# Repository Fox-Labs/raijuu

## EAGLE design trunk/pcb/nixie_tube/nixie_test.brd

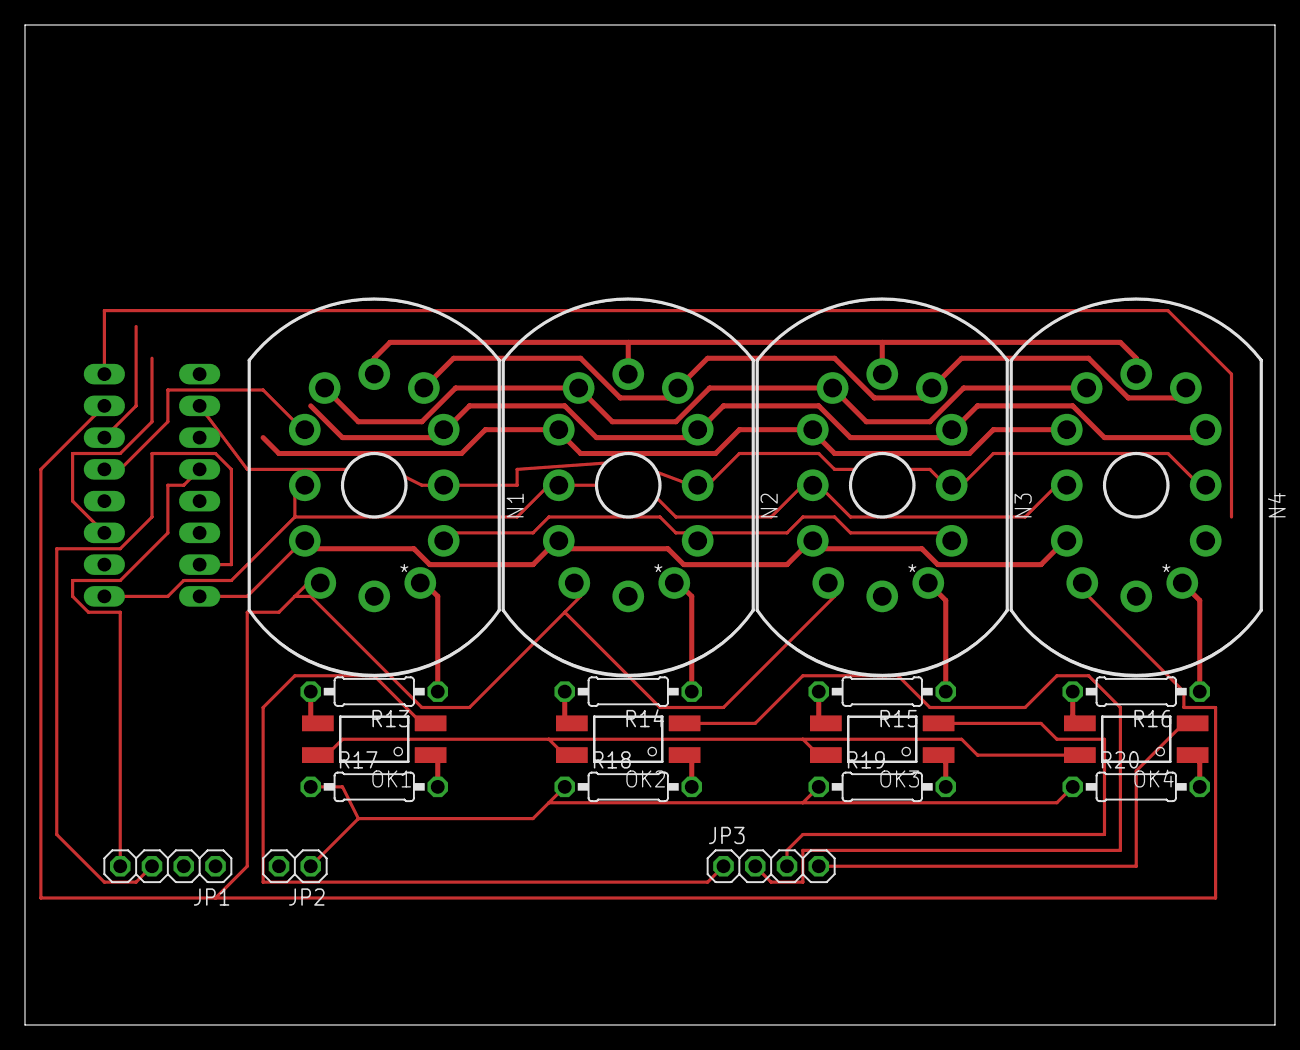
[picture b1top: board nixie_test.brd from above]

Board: 2 copper layers, 100.0 x 80.0 mm, 20 parts (1 on the bottom side), 33 nets.

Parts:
IC1: 74141N; DIL16
JP1, JP3: 1X04
JP2: 1X02
N1, N2, N3, N4: IN-12B; IN-12
OK1, OK2, OK3, OK4: TLP627; 4-SMD
R13, R14, R15, R16, R17, R18, R19, R20: 0207/10

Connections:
+5V: IC1.5, JP2.1, R17.1, R18.1, R19.1, R20.1
+24V: OK1.4, OK2.4, OK3.4, OK4.4
A1: JP3.1, OK1.2
A2: JP3.2, OK2.2
A3: JP3.3, OK3.2
A4: JP3.4, OK4.2
C0: IC1.16, N1.0, N2.0, N3.0, N4.0
C1: IC1.15, N1.1, N2.1, N3.1, N4.1
C2: IC1.8, N1.2, N2.2, N3.2, N4.2
C3: IC1.9, N1.3, N2.3, N3.3, N4.3
C4: IC1.13, N1.4, N2.4, N3.4, N4.4
C5: IC1.14, N1.5, N2.5, N3.5, N4.5
C6: IC1.11, N1.6, N2.6, N3.6, N4.6
C7: IC1.10, N1.7, N2.7, N3.7, N4.7
C8: IC1.1, N1.8, N2.8, N3.8, N4.8
C9: IC1.2, N1.9, N2.9, N3.9, N4.9
GND: IC1.12, JP2.2
unnamed: IC1.3, JP1.1
unnamed: IC1.6, JP1.2
unnamed: IC1.7, JP1.3
unnamed: IC1.4, JP1.4
unnamed: N1.A, R13.1
unnamed: OK1.3, R13.2
unnamed: N2.A, R14.1
unnamed: OK2.3, R14.2
unnamed: N3.A, R15.1
unnamed: OK3.3, R15.2
unnamed: N4.A, R16.1
unnamed: OK4.3, R16.2
unnamed: OK1.1, R17.2
unnamed: OK2.1, R18.2
unnamed: OK3.1, R19.2
unnamed: OK4.1, R20.2

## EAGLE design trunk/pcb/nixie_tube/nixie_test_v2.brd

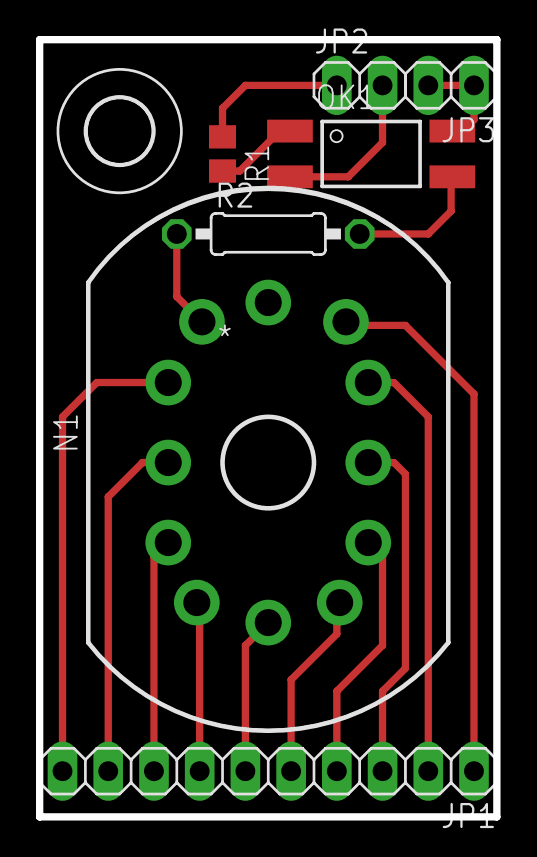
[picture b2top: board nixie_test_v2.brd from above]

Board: 2 copper layers, 25.4 x 43.2 mm, 8 parts (0 on the bottom side), 16 nets.

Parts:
JP1: 1X10
JP2, JP3: 1X02
N1: IN-12B; IN-12
OK1: TLP627; 4-SMD
R1: R0805
R2: 0207/10
U$1: 3,6

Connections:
+5V: JP2.1, R1.1
+24V: JP3.1, JP3.2, OK1.4
C0: JP1.10, N1.0
C1: JP1.1, N1.1
C2: JP1.2, N1.2
C3: JP1.3, N1.3
C4: JP1.4, N1.4
C5: JP1.5, N1.5
C6: JP1.6, N1.6
C7: JP1.7, N1.7
C8: JP1.8, N1.8
C9: JP1.9, N1.9
unnamed: JP2.2, OK1.2
unnamed: N1.A, R2.1
unnamed: OK1.3, R2.2
unnamed: OK1.1, R1.2

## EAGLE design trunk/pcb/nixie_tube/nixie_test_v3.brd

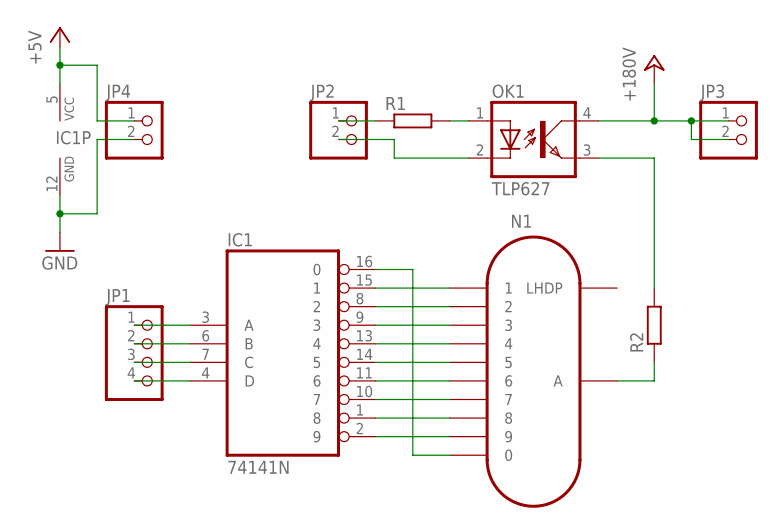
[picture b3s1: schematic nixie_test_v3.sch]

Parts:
IC1: 74141N; DIL16
JP1: PINHD-1X4; 1X04
JP2, JP3, JP4: PINHD-1X2; 1X02
N1: IN-12B; IN-12
OK1: TLP627; 4-SMD
R1: R-EU_R0805; R0805
R2: R-EU_10; 0207/10

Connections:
+5V: IC1.5 (VCC), JP4.1
+180V: JP3.1, JP3.2, OK1.4 (COL)
A: IC1.3 (A), JP1.1
B: IC1.6 (B), JP1.2
C: IC1.7 (C), JP1.3
C0: IC1.16 (0), N1.0
C1: IC1.15 (1), N1.1
C2: IC1.8 (2), N1.2
C3: IC1.9 (3), N1.3
C4: IC1.13 (4), N1.4
C5: IC1.14 (5), N1.5
C6: IC1.11 (6), N1.6
C7: IC1.10 (7), N1.7
C8: IC1.1 (8), N1.8
C9: IC1.2 (9), N1.9
D: IC1.4 (D), JP1.4
GND: IC1.12 (GND), JP4.2
LA: JP2.1, R1.1
LK: JP2.2, OK1.2 (C)
unnamed: N1.A, R2.1
unnamed: OK1.3 (EMIT), R2.2
unnamed: OK1.1 (A), R1.2

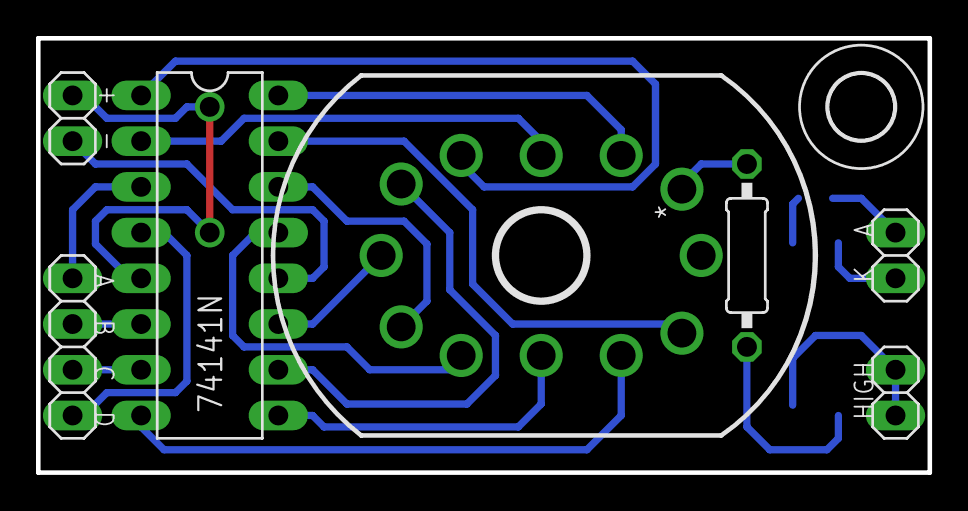
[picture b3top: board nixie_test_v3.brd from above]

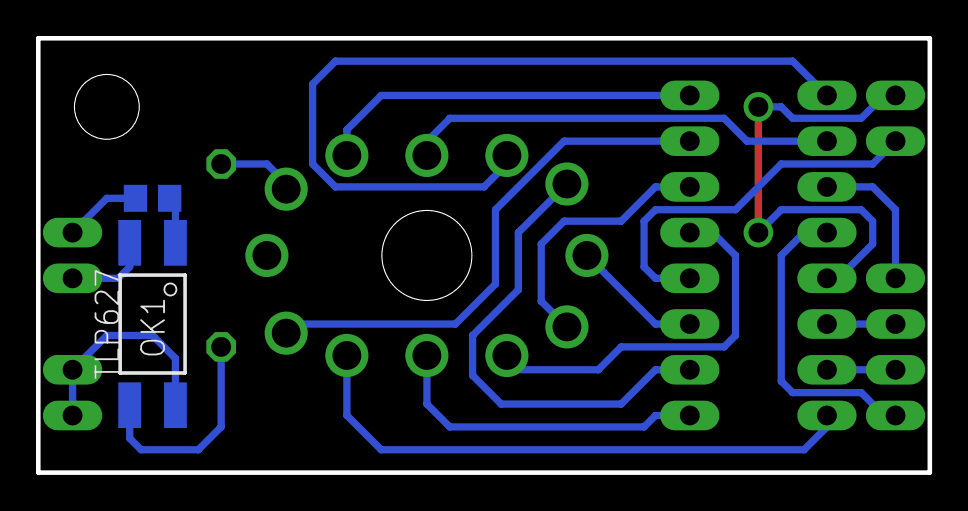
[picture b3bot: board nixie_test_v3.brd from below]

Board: 2 copper layers, 49.5 x 24.1 mm, 10 parts (2 on the bottom side), 22 nets.

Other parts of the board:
U$1: 3,6

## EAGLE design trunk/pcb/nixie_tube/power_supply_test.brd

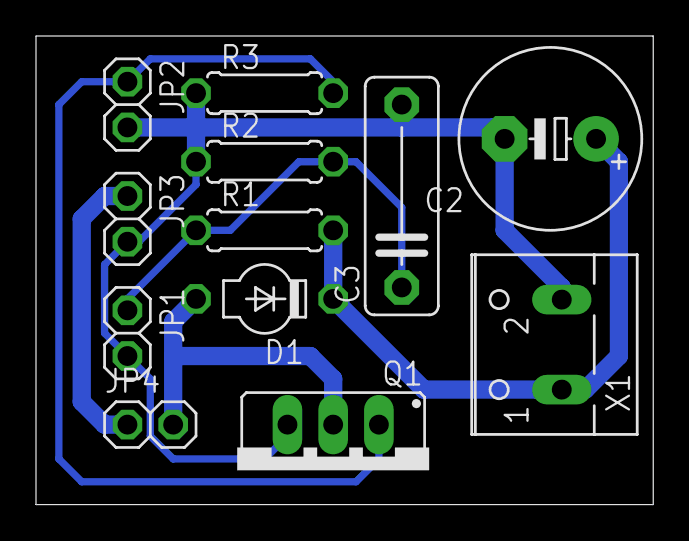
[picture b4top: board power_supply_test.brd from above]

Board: 2 copper layers, 34.3 x 26.0 mm, 12 parts (0 on the bottom side), 6 nets.

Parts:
C2: E5-10,5
C3: C102-043X133
D1: BYV27; SOD57
JP1: SENS; 1X02
JP2: PWM; 1X02
JP3: POWER; 1X02
JP4: IND; 1X02
Q1: IRF840; TO220-A
R1: 680k; 0207/7
R2: 10k; 0207/7
R3: 330; 0207/7
X1: W237-102

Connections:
180: C2.+, D1.C, R1.2, X1.1
+12V: JP3.1, JP4.1
GND: C2.-, C3.2, JP1.2, JP2.2, JP3.2, Q1.3, R2.1, R3.1, X1.2
IND: D1.A, JP4.2, Q1.2
PWM: JP2.1, Q1.1, R3.2
SENS: C3.1, JP1.1, R1.1, R2.2
